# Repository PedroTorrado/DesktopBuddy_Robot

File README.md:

# Project Mimir

An autonomous, reactive, and expressive robotic companion built with an ESP32-CAM and STM32 Nucleo.

## ᛗ Runic Symbolism
The project logo features the Norse rune **Mannaz (ᛗ)** representing humanity and the mind, combined with a central camera lens. This symbolizes the camera's core objective: searching for, tracking, and identifying human faces. The name *Mimir* refers to the wise Norse sentinel head whose well guards Odin's sacrificed eye.

## Features
*   **Neural Network Face Tracking**: Uses the ESP32-CAM to detect faces and dynamically tracks them using a Proportional-Integral (PI) motor loop.
*   **SD Card Wi-Fi Loader & OLED Selector Menu**: Reads custom networks on-the-fly from `/wifi.txt` on a MicroSD card. Allows interactively scanning and joining networks via the Nucleo OLED screen and button long-press.
*   **Dynamic Telemetry Refresh Rate**: Switch between **Eco (5s)** and **Turbo (1s)** refresh modes directly from the web dashboard to control cloud costs or increase responsiveness.
*   **Startup Link Verification**: Automatic serial handshake (`PING/PONG`) on boot to visually confirm TX/RX wire integrity.
*   **Emotion Engine**: A state machine that gives the robot a personality (Happy, Searching, Dizzy, Angry) based on sensor inputs.
*   **Sensory Suite**: Monitors room air quality (SGP30) and avoids collisions with ultrasonic sonar (HC-SR04).
*   **Cloud Telemetry**: Streams data to AWS IoT Core over MQTT.

## Expressive Personalities
Project Mimir uses its SSD1306 OLED display to express its emotions dynamically based on sensor inputs:

### HAPPY (Tracking)
```text
                   ▄█▄                     ▄█▄
                 ▄██▀██▄                 ▄██▀██▄
               ▄██▀   ▀██              ▄██▀   ▀██
               █▀       ▀              █▀       ▀

                      █▄                 ▄
                      ▀██▄             ▄██
                        ▀██▄         ▄██▀
                          ▀██▄     ▄██▀
                            ▀██▄ ▄██▀
                              ▀███▀
                                ▀
```

### ANGRY (Obstacle Alert)
```text
                        ▄█              █▄
                      ▄█▀               ▀██▄
                    ▄█▀                   ▀██▄
                  ▄█▀                       ▀██▄
                ▄█▀                           ▀██▄
               ██████████              ███████████
               ██████████              ██████████
               ██████████              ██████████
               ██████████              ██████████
               ██████████              ██████████

                                   ██████████
```

### DIZZY (Jerk/Bump)
```text
               ▀▄        ▄             ▀▄        ▄
                ▀▄      █               ▀▄      █
                 ▀▄    █                 ▀▄    █
                  ▀▄  █                   ▀▄  █
                   ▀▄█                     ▀▄█
                    █▄                      █▄
                   █ ▀▄                    █ ▀▄
                  █   ▀▄                  █   ▀▄
                 █     ▀▄                █     ▀▄
                █       ▀▄              █       ▀▄
               ▀                       ▀

                              ██   ██
                           ███  ███
```

## Documentation
Please refer to the `docs/` folder for comprehensive setup instructions:
1.  **[System Architecture](docs/system_architecture.md)**: Overview of the dual-microcontroller setup and data flow.
2.  **[Wiring Guide](docs/wiring_guide.md)**: Detailed pin-to-pin wiring for all hardware components.
3.  **[AWS IoT Setup Guide](docs/aws_iot_setup_guide.md)**: Instructions on provisioning cloud certificates and policies.

## Repository Structure
*   `/ESP32_CAM`: Arduino IDE project for the ESP32-CAM vision coprocessor.
*   `/Nucleo_F411RE`: STM32CubeIDE project for the Nucleo master controller.
*   `/docs`: Architecture diagrams and hardware setup guides.

## Quick Start
1. Copy `.env.example` to `.env` and fill in your WiFi and AWS credentials.
2. Copy `ESP32_CAM/secrets.h.example` to `ESP32_CAM/secrets.h` and paste your certificates.
3. Flash the ESP32 using the Arduino IDE.
4. Build and flash the Nucleo using STM32CubeIDE.
5. Refer to `docs/wiring_guide.md` for physical hardware connections.

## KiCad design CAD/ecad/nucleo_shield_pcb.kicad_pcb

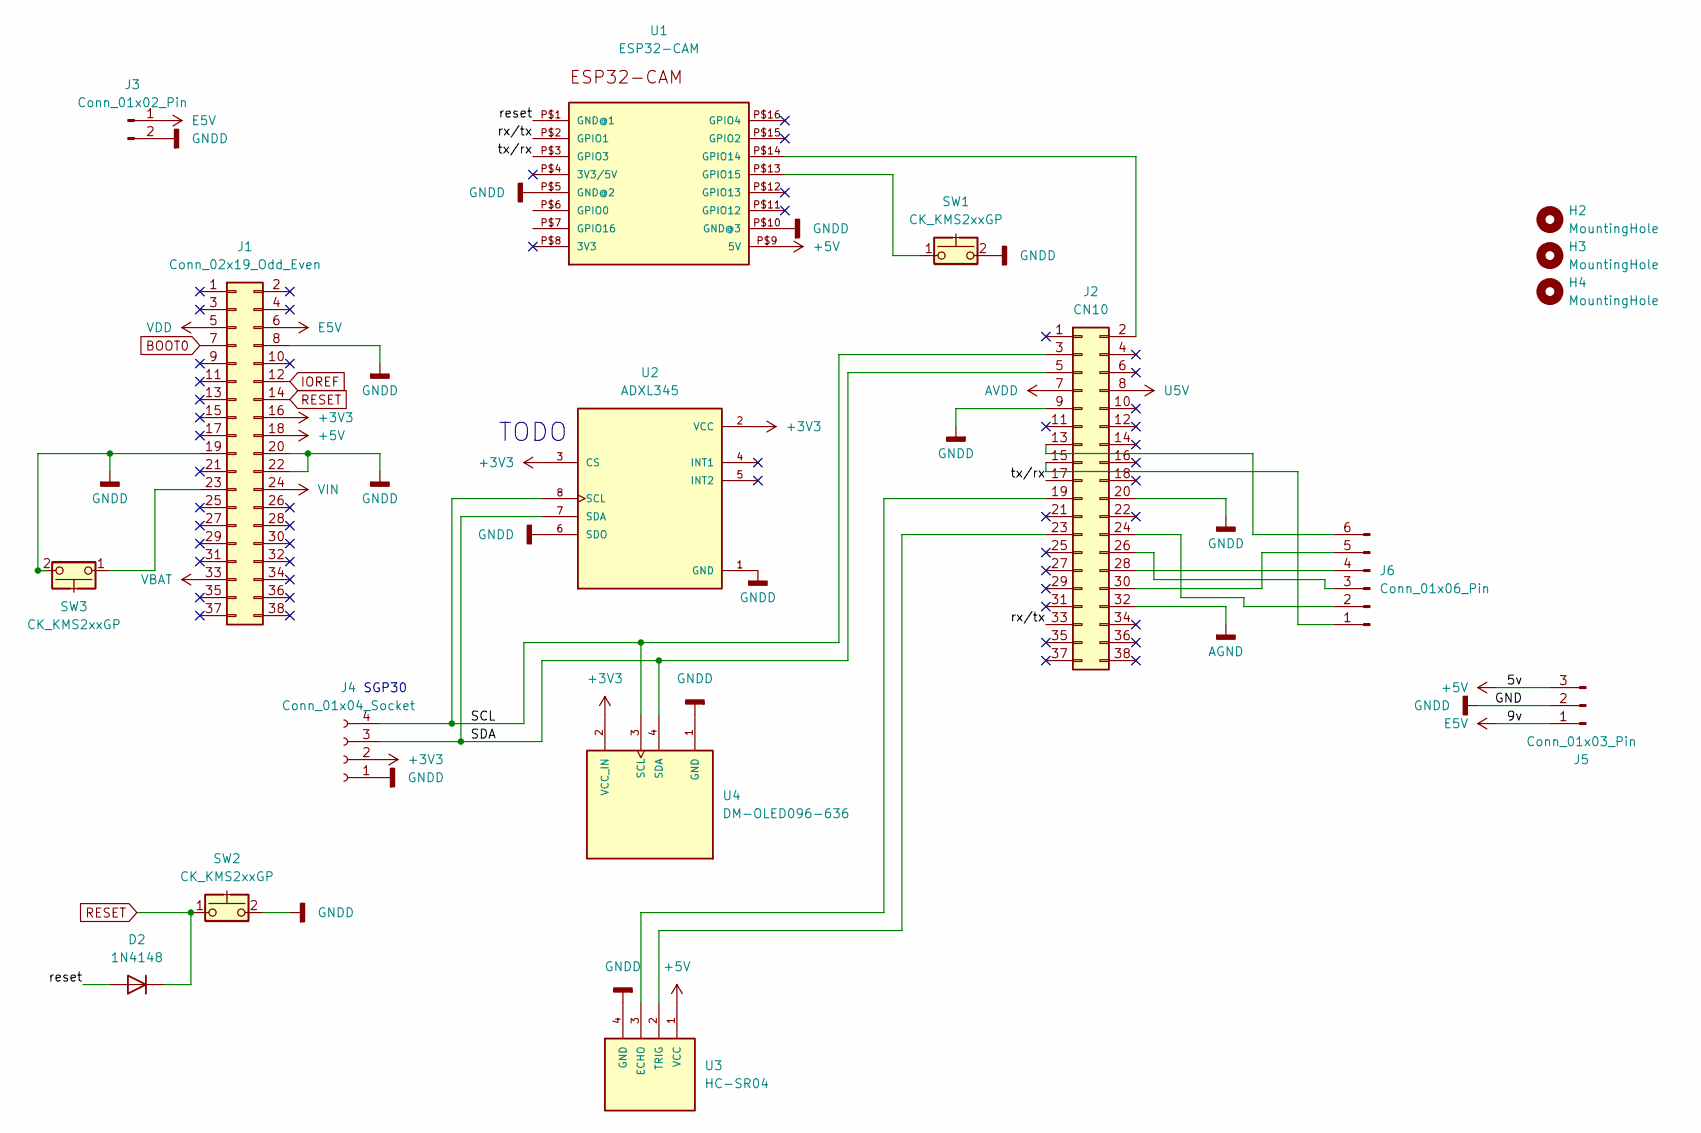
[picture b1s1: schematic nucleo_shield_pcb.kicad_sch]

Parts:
D2: 1N4148; D_DO-35_SOD27_P7.62mm_Horizontal
H2, H3, H4: MountingHole; MountingHole_3.2mm_M3_ISO14580
J1: Conn_02x19_Odd_Even; PinSocket_2x19_P2.54mm_Vertical
J2: CN10; PinSocket_2x19_P2.54mm_Vertical
J3: Conn_01x02_Pin; PinHeader_1x02_P2.54mm_Vertical
J4: Conn_01x04_Socket; JST_PH_B4B-PH-K_1x04_P2.00mm_Vertical
J5: Conn_01x03_Pin; PinHeader_1x03_P1.00mm_Vertical
J6: Conn_01x06_Pin; PinHeader_1x06_P1.27mm_Vertical
SW1, SW2, SW3: CK_KMS2xxGP; SW_SPST_PTS645Sx43SMTR92
U1: ESP32-CAM
U2: ADXL345; MODULE_SEN-09836; PARTREV v14
U3: HC-SR04; XCVR_HC-SR04
U4: DM-OLED096-636; MODULE_DM-OLED096-636; PARTREV 2018-09-10

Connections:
+3V3: J1.16, J4.2, U2.2 (VCC), U2.3 (CS), U4.2 (VCC_IN)
+5V: J1.18, J5.3, U1.P$9 (5V), U3.1 (VCC)
/SCL: J2.3, J4.4, U2.8 (SCL), U4.3 (SCL)
/SDA: J2.5, J4.3, U2.7 (SDA), U4.4 (SDA)
/reset: D2.2 (A), U1.P$1 (GND@1)
/rx/tx: J2.33, U1.P$2 (GPIO1)
/tx/rx: J2.17, U1.P$3 (GPIO3)
AGND: J2.32
AVDD: J2.7
BOOT0: J1.7
E5V: J1.6, J3.1, J5.1
GNDD: J1.8, J1.19, J1.20, J1.22, J2.9, J2.20, J3.2, J4.1, J5.2, SW1.2, SW2.2, SW3.2, U1.P$5 (GND@2), U1.P$10 (GND@3), U2.1 (GND), U2.6 (SDO), U3.4 (GND), U4.1 (GND)
IOREF: J1.12
unnamed: J1.23, SW3.1
unnamed: J2.2, U1.P$14 (GPIO14)
unnamed: J2.13, J6.6
unnamed: J2.15, J6.1
unnamed: J2.19, U3.3 (ECHO)
unnamed: J2.23, U3.2 (TRIG)
unnamed: J2.24, J6.2
unnamed: J2.26, J6.3
unnamed: J2.28, J6.4
unnamed: J2.30, J6.5
unnamed: SW1.1, U1.P$13 (GPIO15)
RESET: D2.1 (K), J1.14, SW2.1
U5V: J2.8
VBAT: J1.33
VDD: J1.5
VIN: J1.24

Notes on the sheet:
TODO
SGP30

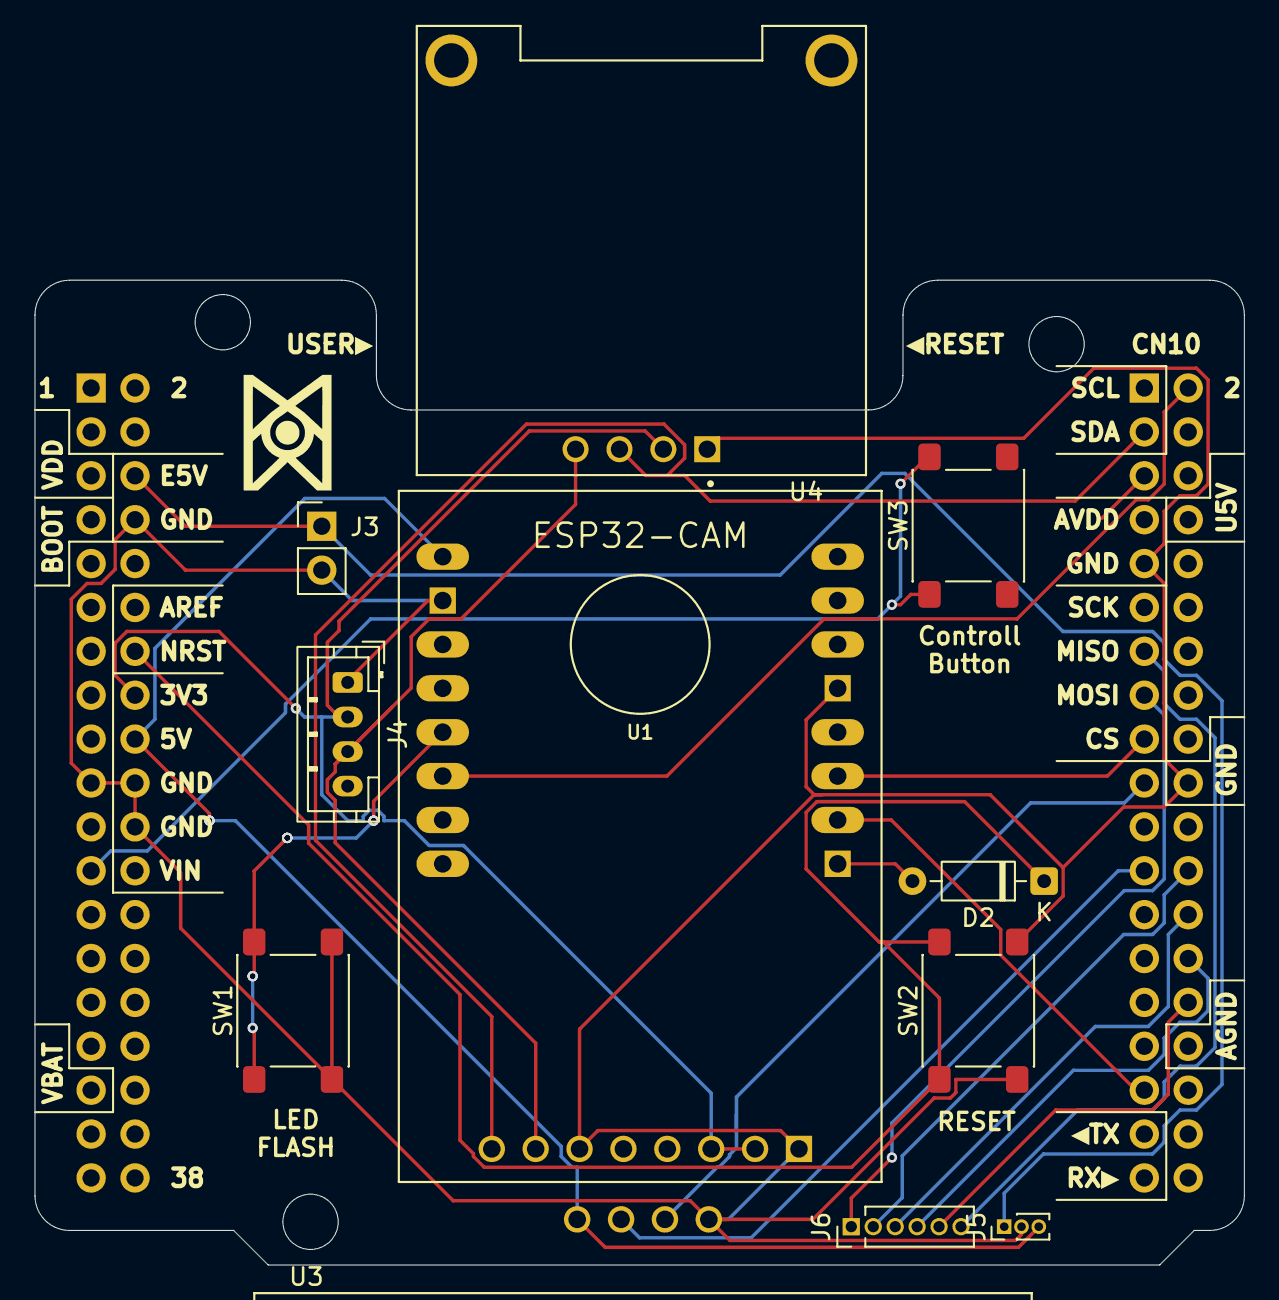
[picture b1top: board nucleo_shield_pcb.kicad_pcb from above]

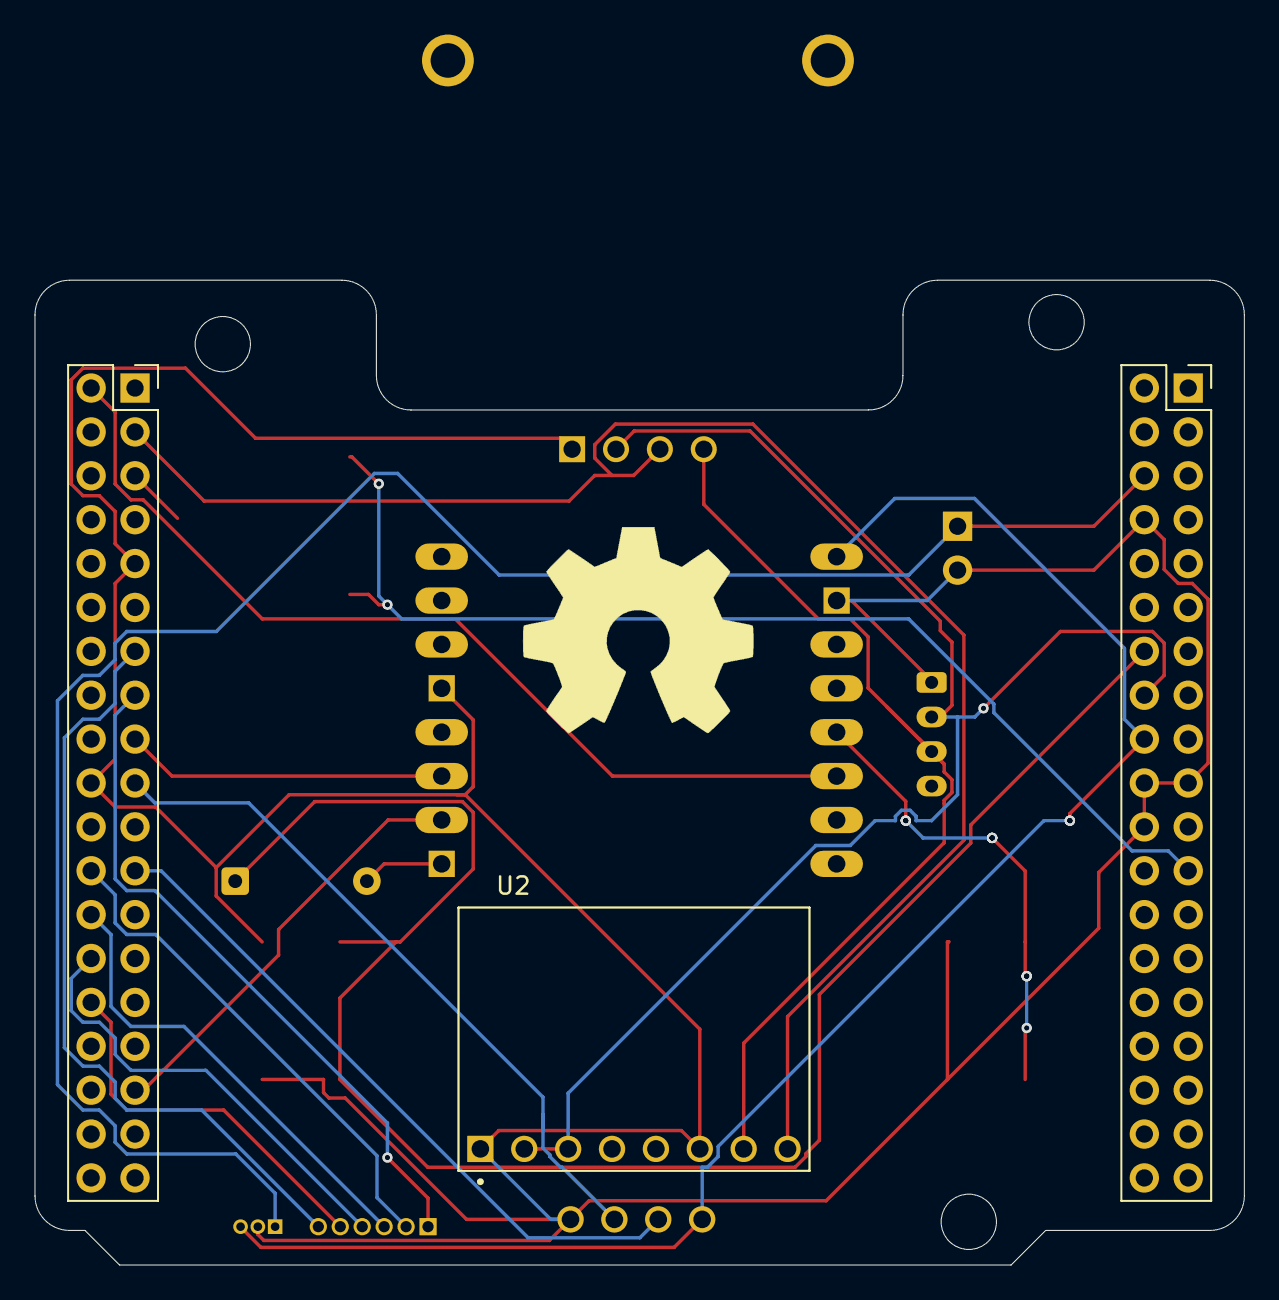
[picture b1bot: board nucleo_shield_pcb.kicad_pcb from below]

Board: 2 copper layers, 70.0 x 57.0 mm, 17 parts (3 on the bottom side), 21 nets.
